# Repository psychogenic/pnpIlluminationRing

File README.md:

# PnP Illumination Ring
Open source hardware illumination ring project, for Charmhigh T36VA pick and place or others.

It's a simple little LED ring that has made a big impact on the reliability of the pick and place machine, 
and I've used it with a number of differently sized fiducials under various lighting conditions to great
success.

I've detailed the project and demoed its function [on youtube](https://youtu.be/Ot52M9ZeZmY).

The project is released under the CERN OHL license, see LICENSE.txt for deets.
```
--------------------------------------------------------------------------------
| Copyright Pat Deegan 2023.                                                   |
|                                                                              |
| This is an Open Hardware project and is licensed under the CERN-OHL-S v2.    |
|                                                                              |
| You may redistribute and modify this source and make products using it under |
| the terms of the CERN-OHL-S v2 (https://ohwr.org/cern_ohl_s_v2.txt).         |
|                                                                              |
| This source is distributed WITHOUT ANY EXPRESS OR IMPLIED WARRANTY,          |
| INCLUDING OF MERCHANTABILITY, SATISFACTORY QUALITY AND FITNESS FOR A         |
| PARTICULAR PURPOSE. Please see the CERN-OHL-S v2 for applicable conditions.  |
|                                                                              |
| Source location: https://github.com/psychogenic/pnpIlluminationRing          |
|                                                                              |
| As per CERN-OHL-S v2 section 4, should You produce hardware based on this    |
| source, You must where practicable maintain the Source Location visible      |
| on the external case of the Gizmo or other products you make using this      |
| source.                                                                      |
--------------------------------------------------------------------------------
```

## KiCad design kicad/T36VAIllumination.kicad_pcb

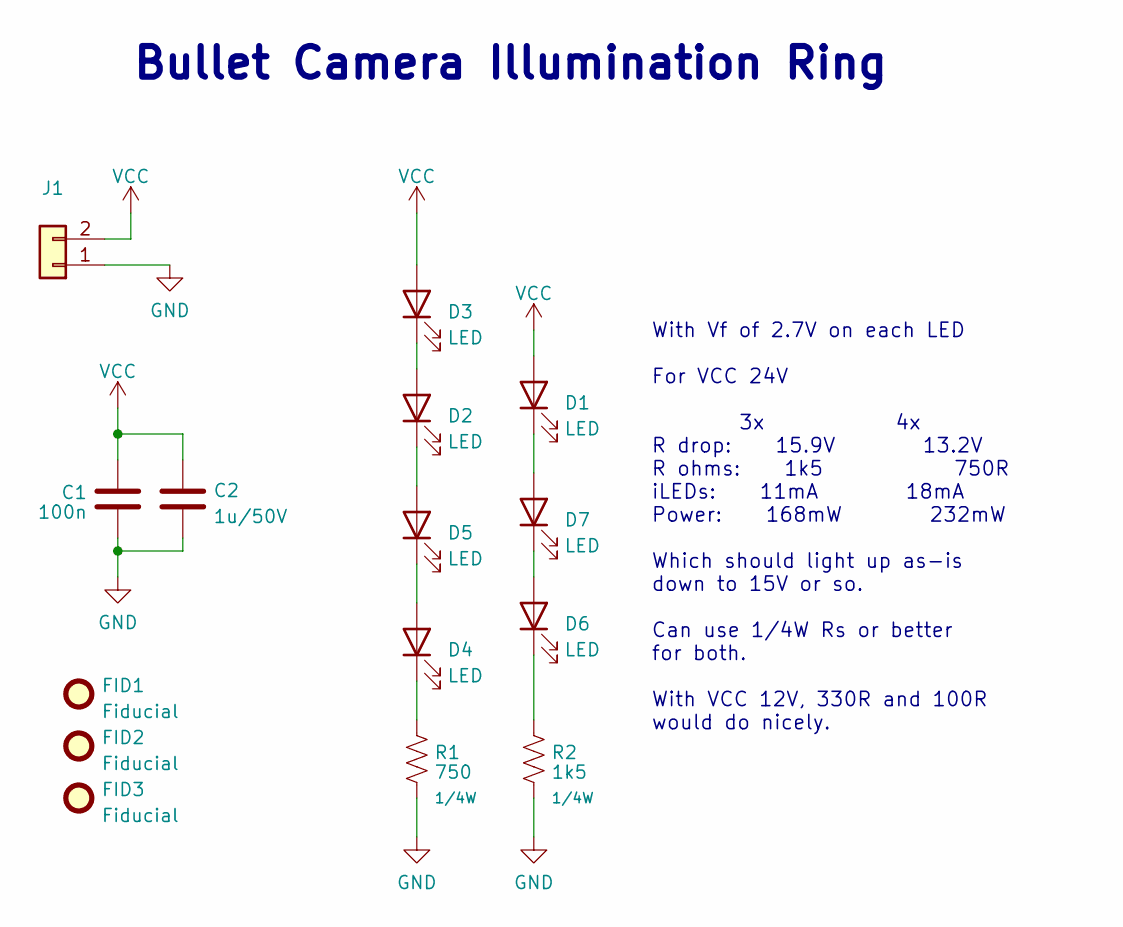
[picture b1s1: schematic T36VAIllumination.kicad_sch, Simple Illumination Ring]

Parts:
C1: C_100n_0603_50V; C_0603_1608Metric
C2: C_1u_0603_50V; C_0603_1608Metric
D1, D2, D3, D4, D5, D6, D7: LED; LED_PLCC-2
FID1, FID2, FID3: Fiducial; Fiducial_1mm_Mask2mm
J1: Conn_01x02; PinHeader_1x02_P2.54mm_Vertical
R1: 750; R_0805_2012Metric
R2: 1k5; R_0805_2012Metric

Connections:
GND: C1.2, C2.2, J1.1, R1.2, R2.2
unnamed: D1.1 (K), D7.2 (A)
unnamed: D2.1 (K), D5.2 (A)
unnamed: D2.2 (A), D3.1 (K)
unnamed: D4.1 (K), R1.1
unnamed: D4.2 (A), D5.1 (K)
unnamed: D6.1 (K), R2.1
unnamed: D6.2 (A), D7.1 (K)
VCC: C1.1, C2.1, D1.2 (A), D3.2 (A), J1.2

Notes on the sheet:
With Vf of 2.7V on each LED For VCC 24V 3x 4x R drop: 15.9V 13.2V R ohms: 1k5 750R iLEDs: 11mA 18mA Power: 168mW 232mW Which should light up as-is down to 15V or so. Can use 1/4W Rs or better for both. With VCC 12V, 330R and 100R would do nicely.
Bullet Camera Illumination Ring

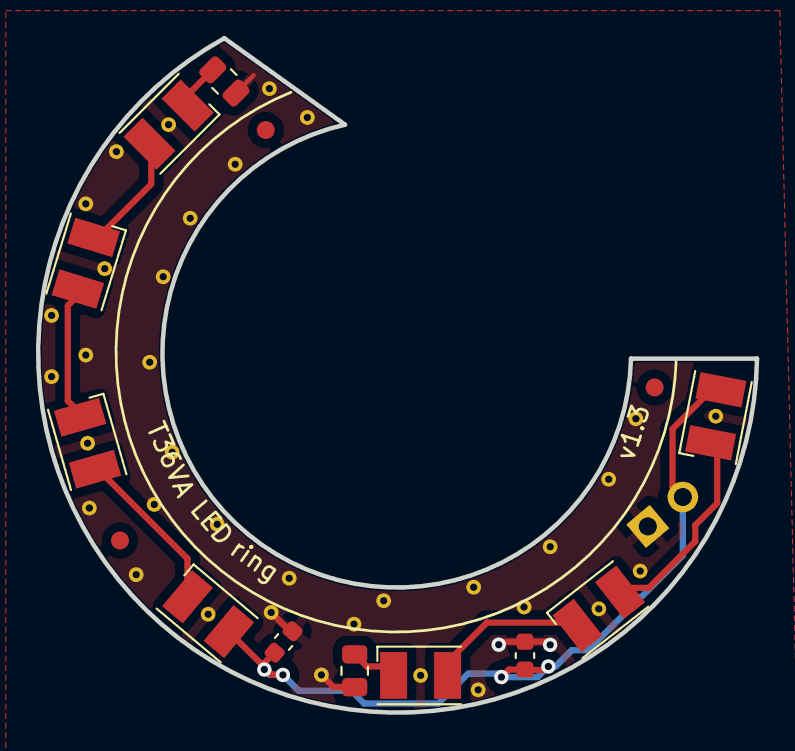
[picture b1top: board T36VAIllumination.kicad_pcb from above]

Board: 2 copper layers, 39.9 x 37.5 mm, 15 parts (1 on the bottom side), 9 nets.

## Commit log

2023-05-20 Initial import
2023-05-20 markdown fix
2023-05-20 More deets, image.
2023-05-20 mardown fix, again

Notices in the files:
kicad/T36VAIllumination.kicad_pcb:
(C) 2023 Pat Deegan
